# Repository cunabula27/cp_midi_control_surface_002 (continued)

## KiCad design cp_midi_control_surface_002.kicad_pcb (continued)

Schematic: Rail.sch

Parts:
J3, J6, J9, J11, J13, J15, J17: Conn_01x38_Male; PinSocket_2x19_P2.54mm_Vertical
J4, J8, J10, J12, J14, J16, J18: Conn_01x38_Female; PinSocket_2x19_P2.54mm_Vertical
J19: Conn_01x18_Male; PinSocket_2x09_P2.54mm_Vertical
J20: Conn_01x18_Female; PinSocket_2x09_P2.54mm_Vertical
J21, J22, J23, J24, J25, J26, J27, J28: Conn_01x01_MountingPin; MountingHole_3.2mm_M3_ISO14580_Pad

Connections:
GND: J6.17, J6.18, J6.19, J6.20, J6.21, J6.22, J8.17, J8.18, J8.19, J8.20, J8.21, J8.22, J11.17, J11.18, J11.19, J11.20, J11.21, J11.22, J12.17, J12.18, J12.19, J12.20, J12.21, J12.22, J15.17, J15.18, J15.19, J15.20, J15.21, J15.22, J16.17, J16.18, J16.19, J16.20, J16.21, J16.22, J19.1, J19.2, J19.3, J19.4, J19.5, J19.6, J19.17, J19.18, J20.1, J20.2, J20.3, J20.4, J20.5, J20.6, J20.17, J20.18, J21.1, J22.1, J23.1, J24.1, J25.1, J26.1, J27.1, J28.1; also elsewhere on the board
unnamed: J3.1, J4.1
unnamed: J3.2, J4.2
unnamed: J3.3, J4.3
unnamed: J3.4, J4.4
unnamed: J3.5, J4.5
unnamed: J3.6, J4.6
unnamed: J3.7, J4.7
unnamed: J3.8, J4.8
unnamed: J3.9, J4.9
unnamed: J3.10, J4.10
unnamed: J3.11, J4.11
unnamed: J3.12, J4.12
unnamed: J3.13, J4.13
unnamed: J3.14, J4.14
unnamed: J3.15, J4.15
unnamed: J3.16, J4.16
unnamed: J3.17, J4.17
unnamed: J3.18, J4.18
unnamed: J3.19, J4.19
unnamed: J3.20, J4.20
unnamed: J3.21, J4.21
unnamed: J3.22, J4.22
unnamed: J3.23, J4.23
unnamed: J3.24, J4.24
unnamed: J3.25, J4.25
unnamed: J3.26, J4.26
unnamed: J3.27, J4.27
unnamed: J3.28, J4.28
unnamed: J3.29, J4.29
unnamed: J3.30, J4.30
unnamed: J3.31, J4.31
unnamed: J3.32, J4.32
unnamed: J3.33, J4.33
unnamed: J3.34, J4.34
unnamed: J3.35, J4.35
unnamed: J3.36, J4.36
unnamed: J3.37, J4.37
unnamed: J3.38, J4.38
unnamed: J6.1, J8.1
unnamed: J6.2, J8.2
unnamed: J6.3, J8.3
unnamed: J6.4, J8.4
unnamed: J6.5, J8.5
unnamed: J6.6, J8.6
unnamed: J6.7, J8.7
unnamed: J6.8, J8.8
unnamed: J6.9, J8.9
unnamed: J6.10, J8.10
unnamed: J6.11, J8.11
unnamed: J6.12, J8.12
unnamed: J6.13, J8.13
unnamed: J6.14, J8.14
unnamed: J6.15, J8.15
unnamed: J6.16, J8.16
unnamed: J6.23, J8.23
unnamed: J6.24, J8.24
unnamed: J6.25, J8.25
unnamed: J6.26, J8.26
unnamed: J6.27, J8.27
unnamed: J6.28, J8.28
unnamed: J6.29, J8.29
unnamed: J6.30, J8.30
unnamed: J6.31, J8.31
unnamed: J6.32, J8.32
unnamed: J6.33, J8.33
unnamed: J6.34, J8.34
unnamed: J6.35, J8.35
unnamed: J6.36, J8.36
unnamed: J6.37, J8.37
unnamed: J6.38, J8.38
unnamed: J9.1, J10.1
unnamed: J9.2, J10.2
unnamed: J9.3, J10.3
unnamed: J9.4, J10.4
unnamed: J9.5, J10.5
unnamed: J9.6, J10.6
unnamed: J9.7, J10.7
unnamed: J9.8, J10.8
unnamed: J9.9, J10.9
unnamed: J9.10, J10.10
unnamed: J9.11, J10.11
unnamed: J9.12, J10.12
unnamed: J9.13, J10.13
unnamed: J9.14, J10.14
unnamed: J9.15, J10.15
unnamed: J9.16, J10.16
unnamed: J9.17, J10.17
unnamed: J9.18, J10.18
unnamed: J9.19, J10.19
unnamed: J9.20, J10.20
unnamed: J9.21, J10.21
unnamed: J9.22, J10.22
unnamed: J9.23, J10.23
unnamed: J9.24, J10.24
unnamed: J9.25, J10.25
unnamed: J9.26, J10.26
unnamed: J9.27, J10.27
unnamed: J9.28, J10.28
unnamed: J9.29, J10.29
unnamed: J9.30, J10.30
unnamed: J9.31, J10.31
unnamed: J9.32, J10.32
unnamed: J9.33, J10.33
unnamed: J9.34, J10.34
unnamed: J9.35, J10.35
unnamed: J9.36, J10.36
unnamed: J9.37, J10.37
unnamed: J9.38, J10.38
unnamed: J11.1, J12.1
unnamed: J11.2, J12.2
unnamed: J11.3, J12.3
unnamed: J11.4, J12.4
unnamed: J11.5, J12.5
unnamed: J11.6, J12.6
unnamed: J11.7, J12.7
unnamed: J11.8, J12.8
unnamed: J11.9, J12.9
unnamed: J11.10, J12.10
unnamed: J11.11, J12.11
unnamed: J11.12, J12.12
unnamed: J11.13, J12.13
unnamed: J11.14, J12.14
unnamed: J11.15, J12.15
unnamed: J11.16, J12.16
unnamed: J11.23, J12.23
unnamed: J11.24, J12.24
unnamed: J11.25, J12.25
unnamed: J11.26, J12.26
unnamed: J11.27, J12.27
unnamed: J11.28, J12.28
unnamed: J11.29, J12.29
unnamed: J11.30, J12.30
unnamed: J11.31, J12.31
unnamed: J11.32, J12.32
unnamed: J11.33, J12.33
unnamed: J11.34, J12.34
unnamed: J11.35, J12.35
unnamed: J11.36, J12.36
unnamed: J11.37, J12.37
unnamed: J11.38, J12.38
unnamed: J13.1, J14.1
unnamed: J13.2, J14.2
unnamed: J13.3, J14.3
unnamed: J13.4, J14.4
unnamed: J13.5, J14.5
unnamed: J13.6, J14.6
unnamed: J13.7, J14.7
unnamed: J13.8, J14.8
unnamed: J13.9, J14.9
unnamed: J13.10, J14.10
unnamed: J13.11, J14.11
unnamed: J13.12, J14.12
unnamed: J13.13, J14.13
unnamed: J13.14, J14.14
unnamed: J13.15, J14.15
unnamed: J13.16, J14.16
unnamed: J13.17, J14.17
unnamed: J13.18, J14.18
unnamed: J13.19, J14.19
unnamed: J13.20, J14.20
unnamed: J13.21, J14.21
unnamed: J13.22, J14.22
unnamed: J13.23, J14.23
unnamed: J13.24, J14.24
unnamed: J13.25, J14.25
unnamed: J13.26, J14.26
unnamed: J13.27, J14.27
unnamed: J13.28, J14.28
unnamed: J13.29, J14.29
unnamed: J13.30, J14.30
unnamed: J13.31, J14.31
unnamed: J13.32, J14.32
unnamed: J13.33, J14.33
unnamed: J13.34, J14.34
unnamed: J13.35, J14.35
unnamed: J13.36, J14.36
unnamed: J13.37, J14.37
unnamed: J13.38, J14.38
unnamed: J15.1, J16.1
unnamed: J15.2, J16.2
unnamed: J15.3, J16.3
unnamed: J15.4, J16.4
unnamed: J15.5, J16.5
unnamed: J15.6, J16.6
unnamed: J15.7, J16.7
unnamed: J15.8, J16.8
unnamed: J15.9, J16.9
unnamed: J15.10, J16.10
unnamed: J15.11, J16.11
unnamed: J15.12, J16.12
unnamed: J15.13, J16.13
unnamed: J15.14, J16.14
unnamed: J15.15, J16.15
unnamed: J15.16, J16.16
unnamed: J15.23, J16.23
unnamed: J15.24, J16.24
unnamed: J15.25, J16.25
unnamed: J15.26, J16.26
unnamed: J15.27, J16.27
unnamed: J15.28, J16.28
unnamed: J15.29, J16.29
unnamed: J15.30, J16.30
unnamed: J15.31, J16.31
unnamed: J15.32, J16.32
unnamed: J15.33, J16.33
unnamed: J15.34, J16.34
unnamed: J15.35, J16.35
unnamed: J15.36, J16.36
unnamed: J15.37, J16.37
unnamed: J15.38, J16.38
unnamed: J17.1, J18.1
unnamed: J17.2, J18.2
unnamed: J17.3, J18.3
unnamed: J17.4, J18.4
unnamed: J17.5, J18.5
unnamed: J17.6, J18.6
unnamed: J17.7, J18.7
unnamed: J17.8, J18.8
unnamed: J17.9, J18.9
unnamed: J17.10, J18.10
unnamed: J17.11, J18.11
unnamed: J17.12, J18.12
unnamed: J17.13, J18.13
unnamed: J17.14, J18.14
unnamed: J17.15, J18.15
unnamed: J17.16, J18.16
unnamed: J17.17, J18.17
unnamed: J17.18, J18.18
unnamed: J17.19, J18.19
unnamed: J17.20, J18.20
unnamed: J17.21, J18.21
unnamed: J17.22, J18.22
unnamed: J17.23, J18.23
unnamed: J17.24, J18.24
unnamed: J17.25, J18.25
unnamed: J17.26, J18.26
unnamed: J17.27, J18.27
unnamed: J17.28, J18.28
unnamed: J17.29, J18.29
unnamed: J17.30, J18.30
unnamed: J17.31, J18.31
unnamed: J17.32, J18.32
unnamed: J17.33, J18.33
unnamed: J17.34, J18.34
unnamed: J17.35, J18.35
unnamed: J17.36, J18.36
unnamed: J17.37, J18.37
unnamed: J17.38, J18.38
unnamed: J19.7, J20.7
unnamed: J19.8, J20.8
unnamed: J19.9, J20.9
unnamed: J19.10, J20.10
unnamed: J19.11, J20.11
unnamed: J19.12, J20.12
unnamed: J19.13, J20.13
unnamed: J19.14, J20.14
unnamed: J19.15, J20.15
unnamed: J19.16, J20.16

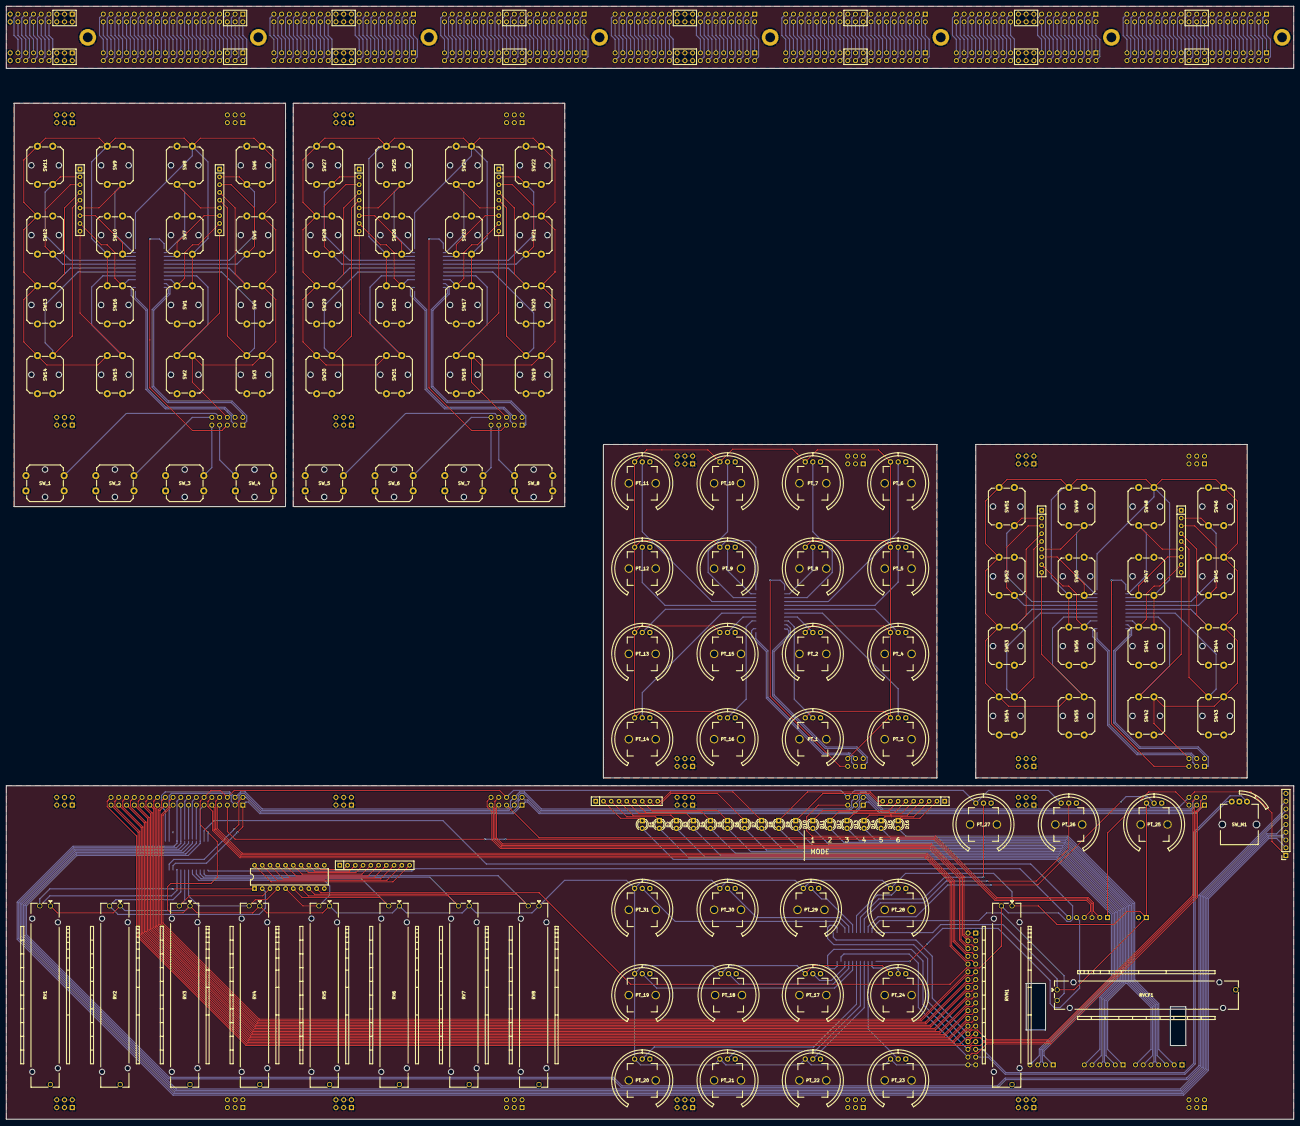
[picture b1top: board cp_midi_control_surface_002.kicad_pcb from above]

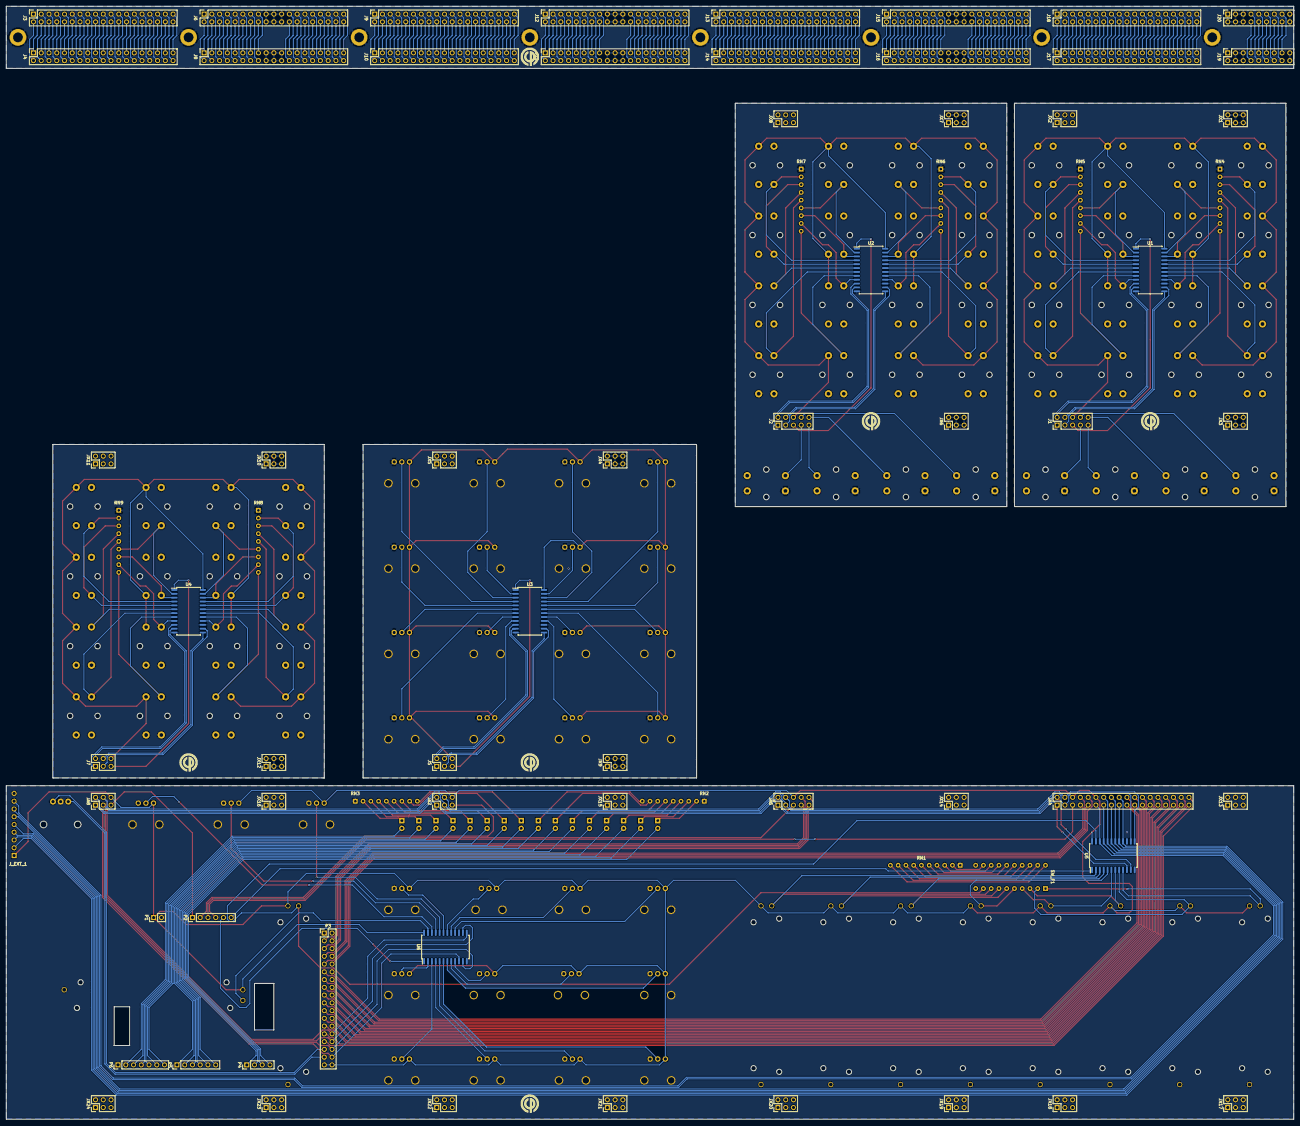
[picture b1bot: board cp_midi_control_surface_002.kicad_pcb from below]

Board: 2 copper layers, 421.6 x 364.5 mm, 198 parts (68 on the bottom side), 463 nets.

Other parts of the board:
J_EXT_1: Conn_01x10; PinSocket_1x09_P2.54mm_Vertical
P8, P9, P11, P12, P13: Guide; Mounting_Hole_M3_Target_Only

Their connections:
+5V: J_EXT_1.1; also elsewhere on the board
/U5_8: J_EXT_1.2; also elsewhere on the board
/U5_9: J_EXT_1.3; also elsewhere on the board
/U5_10: J_EXT_1.4; also elsewhere on the board
/U5_11: J_EXT_1.5; also elsewhere on the board
/U5_12: J_EXT_1.6; also elsewhere on the board
/U5_13: J_EXT_1.7; also elsewhere on the board
/U5_14: J_EXT_1.8; also elsewhere on the board
GND: J_EXT_1.9; also elsewhere on the board

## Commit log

2019-02-19 Transfer of schematic from 002.0
2019-02-19 Initial potentiometer layout
2019-02-20 More initial layout
2019-02-20 Further initial placement
2019-02-20 All panel components placed
2019-02-20 Beginning button connections
    Beginning running traces to the button blocks modified schematic to ensure minimum trace length, rotate buttons to achieve this.
2019-02-21 Further work on the separate boards
2019-02-21 Further connections
2019-02-22 Connected Faders 1-8
2019-02-22 Nothing important
2019-02-22 Revert to panel placement commit
2019-02-22 Revert
2019-02-22 First of changes due to different software
    Moving and analogue inputs, correcting for placement of multiplexer pads.
2019-02-22 Sub boards completed
2019-02-23 Tidy schematic / renumber components / complete daughter boards
2019-02-23 Add copper fill to LED board
2019-02-24 Moved connection to crossfader to ease pin assignment on multiplexer
2019-02-25 Redesign of upper boards
    Added bussed resistors following Igor's correction to the schematic + tidied schematic.
2019-02-25 Further traces added and reassigned duaghter board connection
2019-02-26 Connections complete
    All traces mapped and DRC passed apart from interboard errors - should look into fixing those.
2019-02-27 Cleaning up and rerouting traces
2019-02-27 Revert "Cleaning up and rerouting traces"
    This reverts commit c6a633449036ff81e758f695dc37825436db76d9.
2019-02-27 More rerouting
    Abortive try to reroute LEDs. Looked just as messy the other way round. Other general tidying.
2019-02-28 Added Mounting holes for alternative configuration
    Holes for swapping VCV Buttons for pots
2019-03-02 Positioned all component references on back of boards
2019-07-27 housekeeping
2019-08-06 Beginning the modular redesign
2019-08-06 Added guide lines for the new board shape
2019-08-06 Resize boards and update connector
    Resized the boards to fit the new modular height and started changing the interboard connectors
2019-08-07 Added Rails to Layout
    Found a big problem that the rails are compatible with the boards being modular the way the components are currently spaced.
    Which is a little frustrating.
2019-08-09 COrrected the placement of most of the components for the modular design
    Need to finalise the Arduino placement and work out the design for possible extensions.
2019-08-18 Further cleanup and placement
    Removed all the connectors to the rails as they're irrelevant to the top boards.
    Added all the support headers.
    Need to work out the correct routing for the headers but the placement is correct.
2019-08-21 Forgot to update a couple of components
2019-08-21 Moved two overlapping boards out of the way for clarity and cleaned up folder
2019-08-21 Routing left button blocks (traces for bottom buttons TBD)
2019-08-21 Routing traces on left button block, increased GND plane coverage.
2019-08-21 Routed power to second button board
2019-08-22 All subsidiary boards complete
2019-08-23 Housekeeping
    Cleaned up the schematic for the subsidiary boards
    Switched 5v and Com connections to make routing easier.
2019-08-23 LED resistors placed
2019-08-23 Minor fiddling to adjust ground plane
2019-08-23 Reordered COM contacts and added initial trace positions
2019-08-23 Reinstated extra two pins. Probably coming out again later.
2019-08-23 Bugger, found an error in the S0-S3 rail
2019-08-23 Fixed S0-S3 Rail, added LEDS
    Was an error on the schematic, easily fixed without changing the traces, glad I left it before deleting them all.
    LEDs and relate resistors are in.
2019-08-24 Added external connections / removed unused
    +18 Buttons
    + Different connections for 7 spare multiplexer slots
    - Unused Arduino pins
2019-08-24 Nearly there. Switch placed
2019-08-24 Done - needs a final check and probably some decals and whatnot.
2019-08-24 Rails done, GND corrected.
    Now for checking and decals
2019-08-25 Changed GND plane tightness
    Changed gap between GND plane and traces to 10 mils from 20 mils - allowed me to remove almost all GND vias on the board. Slightly rerooted traces in light of this mainlt spacing them out to allow mo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
2019-08-25 General cleaning up.
    Had a cunning idea, it wasn't cunning, lost an hour.
    Did remove the final GND via on the main board.
2019-08-26 Panel Graphics and logos added
2019-08-26 Little extra fiddling
2019-10-03 Added Baseboard drill guide
2019-10-08 Branch reference update
2019-10-09 Create fp-info-cache
2019-10-09 Cache Update
2019-10-10 Clean up unneeded files now covered by gitignore
2019-10-10 Delete cp_midi_control_surface_002.kicad_pcb-bak
    Unneeded and now covered by gitignore
2019-10-10 Delete cp_midi_control_surface_002.xml
    Unneeded and covered by gitignore
2019-10-10 Update .gitignore
    Reinstate rescue.lib
2019-10-10 Rename files and tidy
2019-10-11 Libs update
2019-10-26 Updated Schematic and changed rotary pots
    Better button symbol and flipped all rotary pots in the schematic so they've connected the right way round.
    Changed the rotary pot footprints so the graphics match the ones I'm using.
2019-10-31 Updated footprints
2019-10-31 Update cp_midi_control_surface_002.kicad_pcb
    Added vias to correct GND plane
2019-10-31 Panel and box guide
